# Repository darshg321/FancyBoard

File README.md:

# FancyBoard

FancyBoard is a custom hot-swappable mechanical keyboard inspired by the k.no.b.1 from Work Louder.

- Hot Swappable
- BlueMicro Firmware
- Low Profile
- Bluetooth & USB-C
- 1.9" IPS Display
- 65% layout
- 2 Dials

i made this keyboard because i saw the KNOB keyboard on reels, and thought it was probably the nicest looking keyboard ive seen, but unfortunately its like 400usd, way too expensive

i wanted to learn how to make a full keyboard after hackpad anyways, so i designed this. i also want a bluetooth keyboard because my current keyboard has a cable thats very annoying, and i wanted to replace it.

## BOM
|Reference             |Value                      |Footprint                                                    |Qty|Link                                                 |Price (USD)|
|----------------------|---------------------------|-------------------------------------------------------------|---|-----------------------------------------------------|-----------|
|C1                    |10uF                       |Capacitor_SMD:C_0603_1608Metric                              |1  |https://www.aliexpress.com/item/1005002761630440.html|3.13       |
|C2,C5,C6              |0.1uF                      |Capacitor_SMD:C_0603_1608Metric                              |3  |                                                     |           |
|D1-D79                |1N4148W                    |Diode_SMD:D_SOD-123                                          |78 |https://www.aliexpress.com/item/1005006123061230.html|2.8        |
|J1                    |Conn_01x02_Socket          |Connector_JST:JST_PH_B2B-PH-K_1x02_P2.00mm_Vertical          |1  |https://www.aliexpress.com/item/1005004955655144.html|2          |
|R1,R6,R7,R8,R9,R10,R11|10K                        |Resistor_SMD:R_0603_1608Metric                               |7  |https://www.aliexpress.com/item/1005008912576822.html|1.9        |
|R2,R3,R4,R5           |4.7K                       |Resistor_SMD:R_0603_1608Metric                               |4  |https://www.aliexpress.com/item/1005008912576822.html|1.9        |
|SW2-SW78              |SW_Push_45deg              |Kailh_PG1353_Hotswap:Kailh-PG1353-Hotswap                    |78 |https://www.aliexpress.com/item/1005008644185126.html|32.61      |
|SW93,SW94             |RotaryEncoder_Switch       |Rotary_Encoder:RotaryEncoder_Alps_EC11E-Switch_Vertical_H20mm|2  |https://www.aliexpress.com/item/1005007644083514.html|2.25       |
|SW95                  |SW_SPDT                    |MSK-12C02:MSK-12C02                                          |1  |https://www.aliexpress.com/item/1005009568929894.html|2.13       |
|U1                    |nice!nanov2                |nice!nanov2:nice!nanov2                                      |1  |https://www.aliexpress.com/item/1005007266112508.html|3.02       |
|U2                    |ST7789_Module              |ST7789_Module:ST7789_Module                                  |1  |https://www.aliexpress.com/item/1005006042323705.html|2.54       |
|U3,U4                 |MCP23017_SO                |Package_SO:SOIC-28W_7.5x17.9mm_P1.27mm                       |2  |https://www.aliexpress.com/item/1005009559642041.html|4.07       |
|                      |Kailh Choc Stabilizers     |                                                             |1  |https://www.aliexpress.com/item/1005006528731543.html|8.65       |
|                      |Kailh Choc Keycaps         |                                                             |78 |https://www.aliexpress.com/item/1005008146995393.html|15.76      |
|                      |Kalih Choc Hot Swap Sockets|                                                             |78 |https://www.aliexpress.com/item/1005006625852715.html|9.73       |
|                      |1s LiPo 500mAh Battery     |                                                             |1  |https://www.aliexpress.com/item/1005007016796736.html|9.15       |
|                      |PCB                        |                                                             |   |https://jlcpcb.com                                   |19         |
|                      |M2 18mm Screw              |                                                             |   |https://www.aliexpress.com/item/1005007264845313.html|1.89       |
|Subtotal              |                           |                                                             |   |                                                     |122.53     |
|AliExpress Shipping   |                           |                                                             |   |                                                     |14.45      |
|JLCPCB Shipping       |                           |                                                             |   |                                                     |13.14      |
|Total                 |                           |                                                             |   |                                                     |150.12     |

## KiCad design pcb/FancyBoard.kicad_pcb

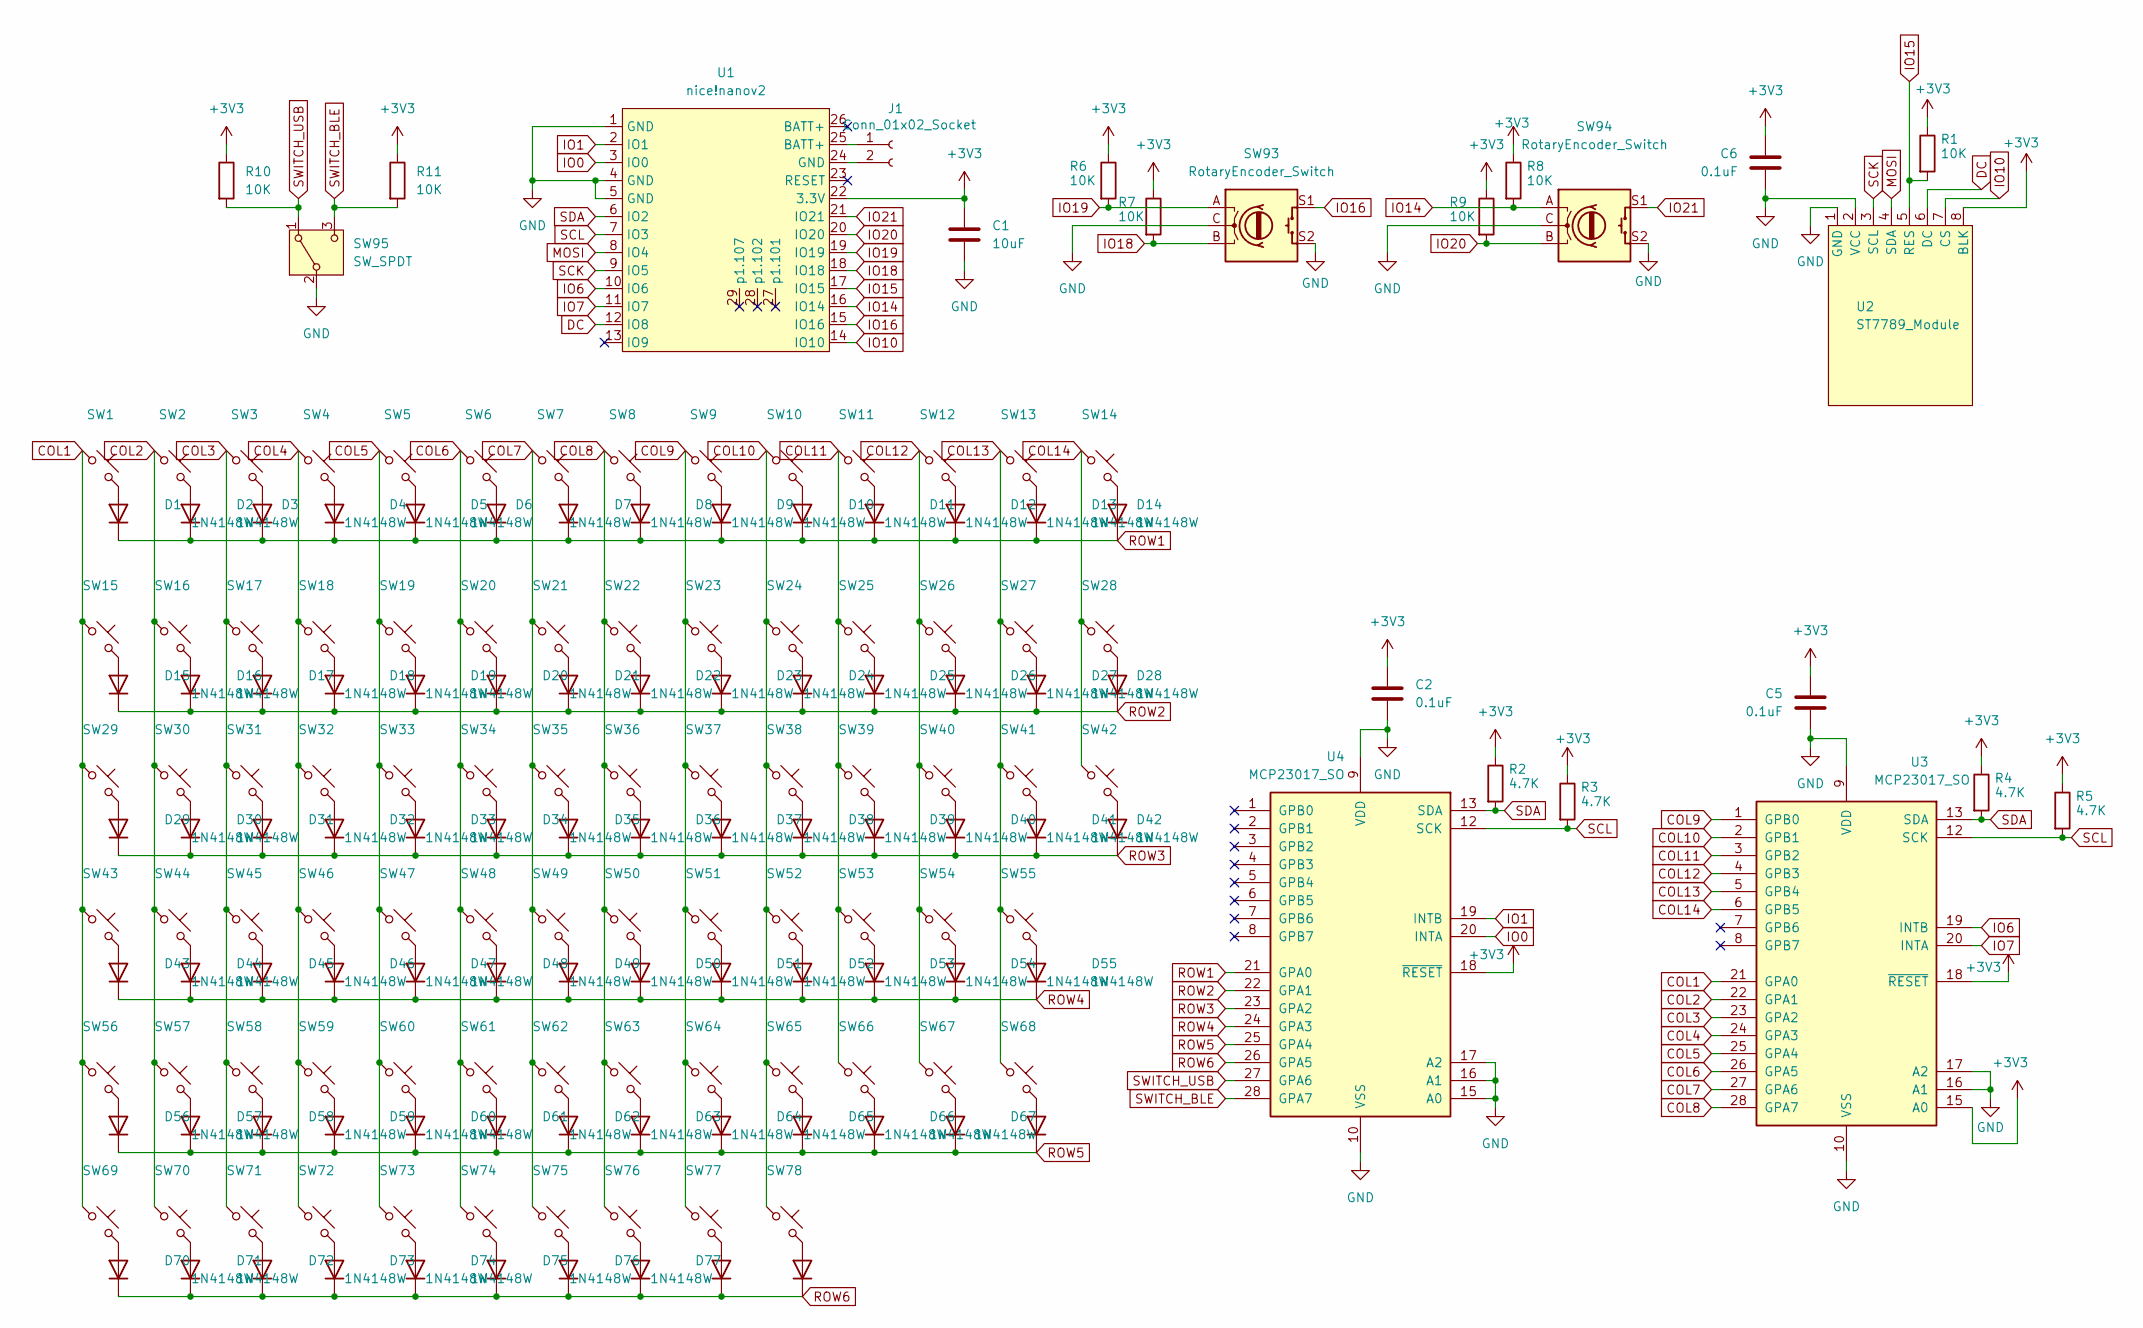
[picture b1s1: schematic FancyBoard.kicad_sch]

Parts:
C1: 10uF; C_0603_1608Metric
C2, C5, C6: 0.1uF; C_0603_1608Metric
D1, D2, D3, D4, D5, D6, D7, D8, D9, D10, D11, D12, D13, D14, D15, D16, D17, D18, D19, D20, D21, D22, D23, D24, D25, D26, D27, D28, D29, D30, D31, D32, D33, D34, D35, D36, D37, D38, D39, D40, D41, D42, D43, D44, D45, D46, D47, D48, D49, D50, D51, D52, D53, D54, D55, D56, D57, D58, D59, D60, D61, D62, D63, D64, D65, D66, D67, D68, D70, D71, D72, D73, D74, D75, D76, D77, D78, D79: 1N4148W; D_SOD-123
J1: Conn_01x02_Socket; JST_PH_B2B-PH-K_1x02_P2.00mm_Vertical
R1, R6, R7, R8, R9, R10, R11: 10K; R_0603_1608Metric
R2, R3, R4, R5: 4.7K; R_0603_1608Metric
SW1, SW14, SW29, SW42: SW_Push_45deg; Kailh-PG1353-Hotswap-1.5U
SW2, SW3, SW4, SW5, SW6, SW7, SW8, SW9, SW10, SW11, SW12, SW13, SW15, SW16, SW17, SW18, SW19, SW20, SW21, SW22, SW23, SW24, SW25, SW26, SW27, SW30, SW31, SW32, SW33, SW34, SW35, SW36, SW37, SW38, SW39, SW40, SW41, SW44, SW45, SW46, SW47, SW48, SW49, SW50, SW51, SW52, SW53, SW54, SW57, SW58, SW59, SW60, SW61, SW62, SW63, SW64, SW65, SW66, SW68, SW73, SW74, SW75, SW76, SW77, SW78: SW_Push_45deg; Kailh-PG1353-Hotswap-1U
SW28: SW_Push_45deg; Kailh-PG1353-Hotswap-2U
SW43, SW67: SW_Push_45deg; Kailh-PG1353-Hotswap-1.75U
SW55, SW56: SW_Push_45deg; Kailh-PG1353-Hotswap-2.25U
SW69, SW70, SW71: SW_Push_45deg; Kailh-PG1353-Hotswap-1.25U
SW72: SW_Push_45deg; Kailh-PG1353-Hotswap-6.25U
SW93, SW94: RotaryEncoder_Switch; RotaryEncoder_Alps_EC11E-Switch_Vertical_H20mm
SW95: SW_SPDT; MSK-12C02
U1: nice!nanov2
U2: ST7789_Module
U3, U4: MCP23017_SO; SOIC-28W_7.5x17.9mm_P1.27mm

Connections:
+3V3: C1.1, C2.1, C5.1, C6.1, R1.1, R2.1, R3.1, R4.1, R5.1, R6.1, R7.1, R8.1, R9.1, R10.1, R11.1, U1.22 (3.3V), U2.8 (BLK), U3.15 (A0), U3.18 (~RESET), U4.18 (~RESET)
COL1: SW1.1, SW15.1, SW29.1, SW43.1, SW56.1, SW69.1, U3.21 (GPA0)
COL2: SW2.1, SW16.1, SW30.1, SW44.1, SW57.1, SW70.1, U3.22 (GPA1)
COL3: SW3.1, SW17.1, SW31.1, SW45.1, SW58.1, SW71.1, U3.23 (GPA2)
COL4: SW4.1, SW18.1, SW32.1, SW46.1, SW59.1, SW72.1, U3.24 (GPA3)
COL5: SW5.1, SW19.1, SW33.1, SW47.1, SW60.1, SW73.1, U3.25 (GPA4)
COL6: SW6.1, SW20.1, SW34.1, SW48.1, SW61.1, SW74.1, U3.26 (GPA5)
COL7: SW7.1, SW21.1, SW35.1, SW49.1, SW62.1, SW75.1, U3.27 (GPA6)
COL8: SW8.1, SW22.1, SW36.1, SW50.1, SW63.1, SW76.1, U3.28 (GPA7)
COL9: SW9.1, SW23.1, SW37.1, SW51.1, SW64.1, SW77.1, U3.1 (GPB0)
COL10: SW10.1, SW24.1, SW38.1, SW52.1, SW65.1, SW78.1, U3.2 (GPB1)
COL11: SW11.1, SW25.1, SW39.1, SW53.1, SW66.1, U3.3 (GPB2)
COL12: SW12.1, SW26.1, SW40.1, SW54.1, SW67.1, U3.4 (GPB3)
COL13: SW13.1, SW27.1, SW41.1, SW55.1, SW68.1, U3.5 (GPB4)
COL14: SW14.1, SW28.1, SW42.1, U3.6 (GPB5)
DC: U1.12 (IO8), U2.6 (DC)
GND: C1.2, C2.2, C5.2, C6.2, SW93.C, SW93.S2, SW94.C, SW94.S2, SW95.2 (B), U1.1 (GND), U1.4 (GND), U1.5 (GND), U2.1 (GND), U2.2 (VCC), U3.9 (VDD), U3.10 (VSS), U3.16 (A1), U3.17 (A2), U4.9 (VDD), U4.10 (VSS), U4.15 (A0), U4.16 (A1), U4.17 (A2)
IO0: U1.3 (IO0), U4.20 (INTA)
IO1: U1.2 (IO1), U4.19 (INTB)
IO6: U1.10 (IO6), U3.19 (INTB)
IO7: U1.11 (IO7), U3.20 (INTA)
IO10: U1.14 (IO10), U2.7 (CS)
IO14: R8.2, SW94.A, U1.16 (IO14)
IO15: R1.2, U1.17 (IO15), U2.5 (RES)
IO16: SW93.S1, U1.15 (IO16)
IO18: R7.2, SW93.B, U1.18 (IO18)
IO19: R6.2, SW93.A, U1.19 (IO19)
IO20: R9.2, SW94.B, U1.20 (IO20)
IO21: SW94.S1, U1.21 (IO21)
MOSI: U1.8 (IO4), U2.4 (SDA)
unnamed: D1.2 (A), SW1.2
unnamed: D2.2 (A), SW2.2
unnamed: D3.2 (A), SW3.2
unnamed: D4.2 (A), SW4.2
unnamed: D5.2 (A), SW5.2
unnamed: D6.2 (A), SW6.2
unnamed: D7.2 (A), SW7.2
unnamed: D8.2 (A), SW8.2
unnamed: D9.2 (A), SW9.2
unnamed: D10.2 (A), SW10.2
unnamed: D11.2 (A), SW11.2
unnamed: D12.2 (A), SW12.2
unnamed: D13.2 (A), SW13.2
unnamed: D14.2 (A), SW14.2
unnamed: D15.2 (A), SW15.2
unnamed: D16.2 (A), SW16.2
unnamed: D17.2 (A), SW17.2
unnamed: D18.2 (A), SW18.2
unnamed: D19.2 (A), SW19.2
unnamed: D20.2 (A), SW20.2
unnamed: D21.2 (A), SW21.2
unnamed: D22.2 (A), SW22.2
unnamed: D23.2 (A), SW23.2
unnamed: D24.2 (A), SW24.2
unnamed: D25.2 (A), SW25.2
unnamed: D26.2 (A), SW26.2
unnamed: D27.2 (A), SW27.2
unnamed: D28.2 (A), SW28.2
unnamed: D29.2 (A), SW29.2
unnamed: D30.2 (A), SW30.2
unnamed: D31.2 (A), SW31.2
unnamed: D32.2 (A), SW32.2
unnamed: D33.2 (A), SW33.2
unnamed: D34.2 (A), SW34.2
unnamed: D35.2 (A), SW35.2
unnamed: D36.2 (A), SW36.2
unnamed: D37.2 (A), SW37.2
unnamed: D38.2 (A), SW38.2
unnamed: D39.2 (A), SW39.2
unnamed: D40.2 (A), SW40.2
unnamed: D41.2 (A), SW41.2
unnamed: D42.2 (A), SW42.2
unnamed: D43.2 (A), SW43.2
unnamed: D44.2 (A), SW44.2
unnamed: D45.2 (A), SW45.2
unnamed: D46.2 (A), SW46.2
unnamed: D47.2 (A), SW47.2
unnamed: D48.2 (A), SW48.2
unnamed: D49.2 (A), SW49.2
unnamed: D50.2 (A), SW50.2
unnamed: D51.2 (A), SW51.2
unnamed: D52.2 (A), SW52.2
unnamed: D53.2 (A), SW53.2
unnamed: D54.2 (A), SW54.2
unnamed: D55.2 (A), SW55.2
unnamed: D56.2 (A), SW56.2
unnamed: D57.2 (A), SW57.2
unnamed: D58.2 (A), SW58.2
unnamed: D59.2 (A), SW59.2
unnamed: D60.2 (A), SW60.2
unnamed: D61.2 (A), SW61.2
unnamed: D62.2 (A), SW62.2
unnamed: D63.2 (A), SW63.2
unnamed: D64.2 (A), SW64.2
unnamed: D65.2 (A), SW65.2
unnamed: D66.2 (A), SW66.2
unnamed: D67.2 (A), SW67.2
unnamed: D68.2 (A), SW68.2
unnamed: D70.2 (A), SW69.2
unnamed: D71.2 (A), SW70.2
unnamed: D72.2 (A), SW71.2
unnamed: D73.2 (A), SW72.2
unnamed: D74.2 (A), SW73.2
unnamed: D75.2 (A), SW74.2
unnamed: D76.2 (A), SW75.2
unnamed: D77.2 (A), SW76.2
unnamed: D78.2 (A), SW77.2
unnamed: D79.2 (A), SW78.2
unnamed: J1.1, U1.25 (BATT+)
unnamed: J1.2, U1.24 (GND)
ROW1: D1.1 (K), D2.1 (K), D3.1 (K), D4.1 (K), D5.1 (K), D6.1 (K), D7.1 (K), D8.1 (K), D9.1 (K), D10.1 (K), D11.1 (K), D12.1 (K), D13.1 (K), D14.1 (K), U4.21 (GPA0)
ROW2: D15.1 (K), D16.1 (K), D17.1 (K), D18.1 (K), D19.1 (K), D20.1 (K), D21.1 (K), D22.1 (K), D23.1 (K), D24.1 (K), D25.1 (K), D26.1 (K), D27.1 (K), D28.1 (K), U4.22 (GPA1)
ROW3: D29.1 (K), D30.1 (K), D31.1 (K), D32.1 (K), D33.1 (K), D34.1 (K), D35.1 (K), D36.1 (K), D37.1 (K), D38.1 (K), D39.1 (K), D40.1 (K), D41.1 (K), D42.1 (K), U4.23 (GPA2)
ROW4: D43.1 (K), D44.1 (K), D45.1 (K), D46.1 (K), D47.1 (K), D48.1 (K), D49.1 (K), D50.1 (K), D51.1 (K), D52.1 (K), D53.1 (K), D54.1 (K), D55.1 (K), U4.24 (GPA3)
ROW5: D56.1 (K), D57.1 (K), D58.1 (K), D59.1 (K), D60.1 (K), D61.1 (K), D62.1 (K), D63.1 (K), D64.1 (K), D65.1 (K), D66.1 (K), D67.1 (K), D68.1 (K), U4.25 (GPA4)
ROW6: D70.1 (K), D71.1 (K), D72.1 (K), D73.1 (K), D74.1 (K), D75.1 (K), D76.1 (K), D77.1 (K), D78.1 (K), D79.1 (K), U4.26 (GPA5)
SCK: U1.9 (IO5), U2.3 (SCL)
SCL: R3.2, R5.2, U1.7 (IO3), U3.12 (SCK), U4.12 (SCK)
SDA: R2.2, R4.2, U1.6 (IO2), U3.13 (SDA), U4.13 (SDA)
SWITCH_BLE: R11.2, SW95.3 (C), U4.28 (GPA7)
SWITCH_USB: R10.2, SW95.1 (A), U4.27 (GPA6)

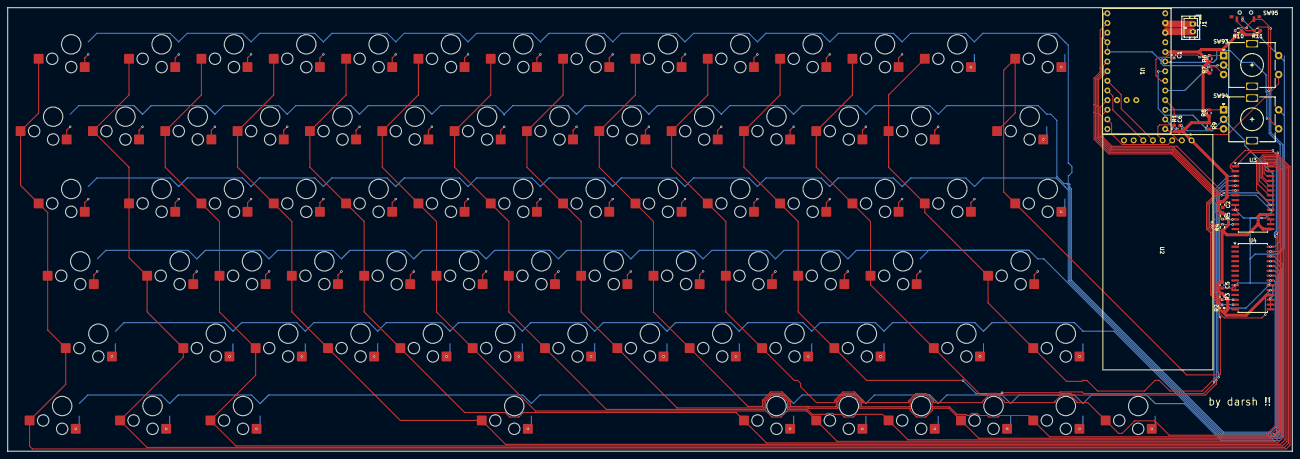
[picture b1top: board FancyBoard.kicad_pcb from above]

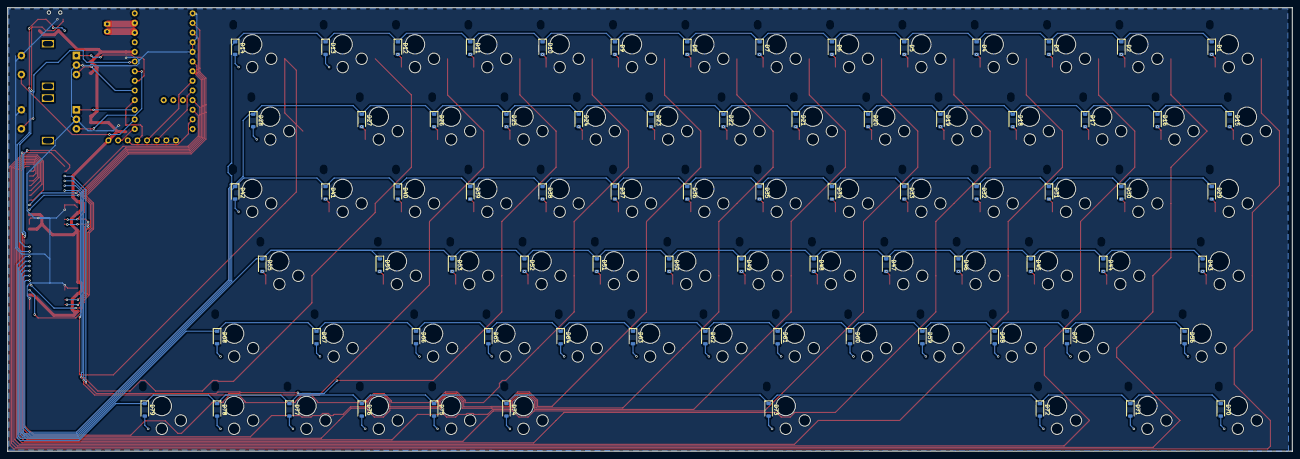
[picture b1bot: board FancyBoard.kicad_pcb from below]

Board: 2 copper layers, 338.3 x 116.8 mm, 179 parts (78 on the bottom side), 121 nets.

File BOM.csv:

Reference,Name,Qty,Price (USD),Link
C1,C 10uF,1,6.04,https://www.aliexpress.com/item/1005007374509699.html
C2,C5,C6,C 0.1uF,3,,https://www.aliexpress.com/item/1005007374509699.html
D1–D79,D 1N4148W,78,3.71,https://www.aliexpress.com/item/1005006123061230.html
J1,JST Conn_01x02_Socket,1,2.55,https://www.aliexpress.com/item/1005004955655144.html
R1,R6,R7,R8,R9,R10,R11,R 10K,7,2.3,https://www.aliexpress.com/item/1005008912576822.html
R2,R3,R4,R5,R 4.7K,4,2.3,https://www.aliexpress.com/item/1005008912576822.html
SW1–SW94,Sunset Tactile Choc Switches,81,62,https://lowprokb.ca/products/sunset-tactile-choc-switches?va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
U1,nice!nanov2,1,26.5,https://typeractive.xyz/products/nice-nano
U2,ST7789_Module,1,6.99,https://www.aliexpress.com/item/1005009445748262.html
U3,U4,MCP23017,2,5.63,https://www.aliexpress.com/item/1005009559642041.html
SW93,SW94,RotaryEncoder_Switch,2,3.11,https://www.aliexpress.com/item/1005007644083514.html
SW95,MSK-12C02,1,2.95,https://www.aliexpress.com/item/1005009568929894.html
,Kailh Choc Stabilizers,1,5,https://lowprokb.ca/products/kailh-choc-stabilizers?variant=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
,Kalih Choc Hot Swap Sockets,81,13.48,https://www.aliexpress.com/item/1005006625852715.html
,Kalih Keycaps,81,32.60,https://lowprokb.ca/products/mbk-low-profile-pbt-blank-keyca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

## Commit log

2025-07-29 most of schematic done
2025-07-29 schematic done
2025-07-30 mostly done pcb
2025-07-30 mostly done routing
2025-07-30 pcb done?
2025-07-31 pcb done
2025-07-31 cad mostly done
2025-08-01 firmware and cad
2025-08-01 finished !!
2025-08-01 filleted + appearance + render
2025-08-02 added more design and new render
2025-08-05 added more to case
2025-08-07 added mounting holes
2025-10-13 removed firmware
2025-10-16 zmk config
